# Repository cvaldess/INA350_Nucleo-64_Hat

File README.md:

# INA350 Nucleo-64 Hat

Test board that plugs onto an STM32 **NUCLEO-64** through the morpho connectors. It compares three
instrumentation amplifiers measuring the **same current shunt**:

- **TI INA350CDS** (U8)
- **Analog Devices AD8220** (U6)
- **Microchip MCP6N11-010** (U7)

The board reproduces one range of a current-measurement front end (shunt, bypass MOSFET and
protection). The three amplifiers can then be compared on real hardware before choosing one for a
power-measurement module. No oscilloscope is needed: the Nucleo is meant to sample the three outputs
at the same time with its own ADCs, synchronised with a load-step timer, and send the results over USB.

*Concept image, not a photo of an assembled board.*

| PCB layout | 3D view |
|---|---|
|  |  |

## Status

**Rev 0.1**: design finished and fabrication files generated. Not yet assembled or tested.
The test firmware is not written yet.

## Features

- Three amplifier channels (rows A, B, C) on one 4.99 kΩ 0.1 % shunt (R11, between VM and VOUT),
  each with its own Kelvin connection to the shunt.
- Shunt bypass MOSFET (Q1, AO3400A) driven by a UCC27524 gate driver (U4), controlled by the Nucleo.
- Loads on VOUT selected with jumpers JP2–JP6, including a step load (Q2 + R16 33 Ω, about 100 mA at
  3.3 V) switched by a timer output.
- Programmable measured voltage VM: adjustable TLV76701 LDO with the Nucleo DAC injected into its
  feedback (about 0.8 V to 5.3 V). Open JP1 to feed an external VM on J2 instead.
- Local rails from 12 V: +10V_G and +5V5_A (TLV76701 LDOs). A TLV9002 buffers the 0.30 V amplifier
  reference and VOUT.
- 12 V input through a DC jack (J5) or a 2-pin header (J1), with an SS34 series diode and a 470 µF bulk
  capacitor.
- Test points on every relevant node and six jumpers to configure the channels.

## Board

- 70 × 53 mm, 4 layers (In1 power, In2 signal), green solder mask.
- 2×19 sockets (HC-PM254-8.5H) on the bottom side; the board sits about 11 mm above the Nucleo.
- Two 3 mm notches on the top edge leave room for the Nucleo user and reset buttons (B1/B2).
- Fine-pitch parts use `_PCBWay` footprint variants (solder-mask web ≥ 0.19 mm between pads).

## Compatible Nucleo boards

| Board | Notes |
|---|---|
| NUCLEO-G474RE (MB1367) | Move **JP8 to [2-3]** so that VREF+ = VDD. With the factory VREF+ of 2.5 V the full output range does not fit. |
| NUCLEO-G564RE (MB2067) | Works as is. The DAC output is on PA5 instead of PA4. |

No solder bridges need to be changed on either board.

## Nucleo pin mapping

| Signal | Morpho pin | MCU pin | Use |
|---|---|---|---|
| O_A, AD8220 output | CN7-30 | PA1 | ADC / COMP1 |
| O_B, MCP6N11-010 output | CN7-28 | PA0 | ADC / COMP3 |
| O_C, INA350 output | CN7-34 | PB0 | ADC / COMP4 |
| DAC_VM, VM setpoint | CN7-32 | PA4 (G474RE) / PA5 (G564RE) | DAC |
| VOUT_S, output voltage sense | CN7-36 | PC1 | ADC |
| VM_S, VM sense | CN7-38 | PC0 | ADC |
| LOAD, load step | CN10-31 | PB3 | TIM2_CH2 |
| BYP0, shunt bypass | CN10-5 | PB9 | GPIO |
| +3V3 | CN7-16 | | |
| GND | CN7-8/19/20/22, CN10-9/20 | | |

## Repository layout

```
kicad/                          KiCad 10 project (schematic, PCB, design rules)
kicad/lib/                      project libraries: symbols, footprints and 3D models used by the board
fabrication/2026-11-17_rev0.1/  Gerbers + drill files (folder and zip), BOM, pick-and-place
images/                         README images
```

Open `kicad/PRUEBA_INA.kicad_pro` with **KiCad 10.0** or newer. The project keeps its original internal
name (`PRUEBA_INA`, Spanish for "INA test"). Part of the schematic text is in Spanish.

## Manufacturing notes

- `PRUEBA_INA_gerbers.zip` is ready to upload to a PCB fab (4 layers, 1.6 mm).
- The BOM lists LCSC part numbers where available. Generic 0603 passives have no part number.
- Test points are pads only and are not in the BOM.

## License

Copyright © 2026 CValdesS.com

This hardware design is licensed under the **CERN Open Hardware Licence Version 2 – Strongly
Reciprocal** (CERN-OHL-S-2.0). See [LICENSE](LICENSE).

Footprints and 3D models in `kicad/lib/easyeda2kicad.*` were converted from the LCSC/EasyEDA library
with [easyeda2kicad](https://github.com/uPesy/easyeda2kicad.py) and are included for convenience.

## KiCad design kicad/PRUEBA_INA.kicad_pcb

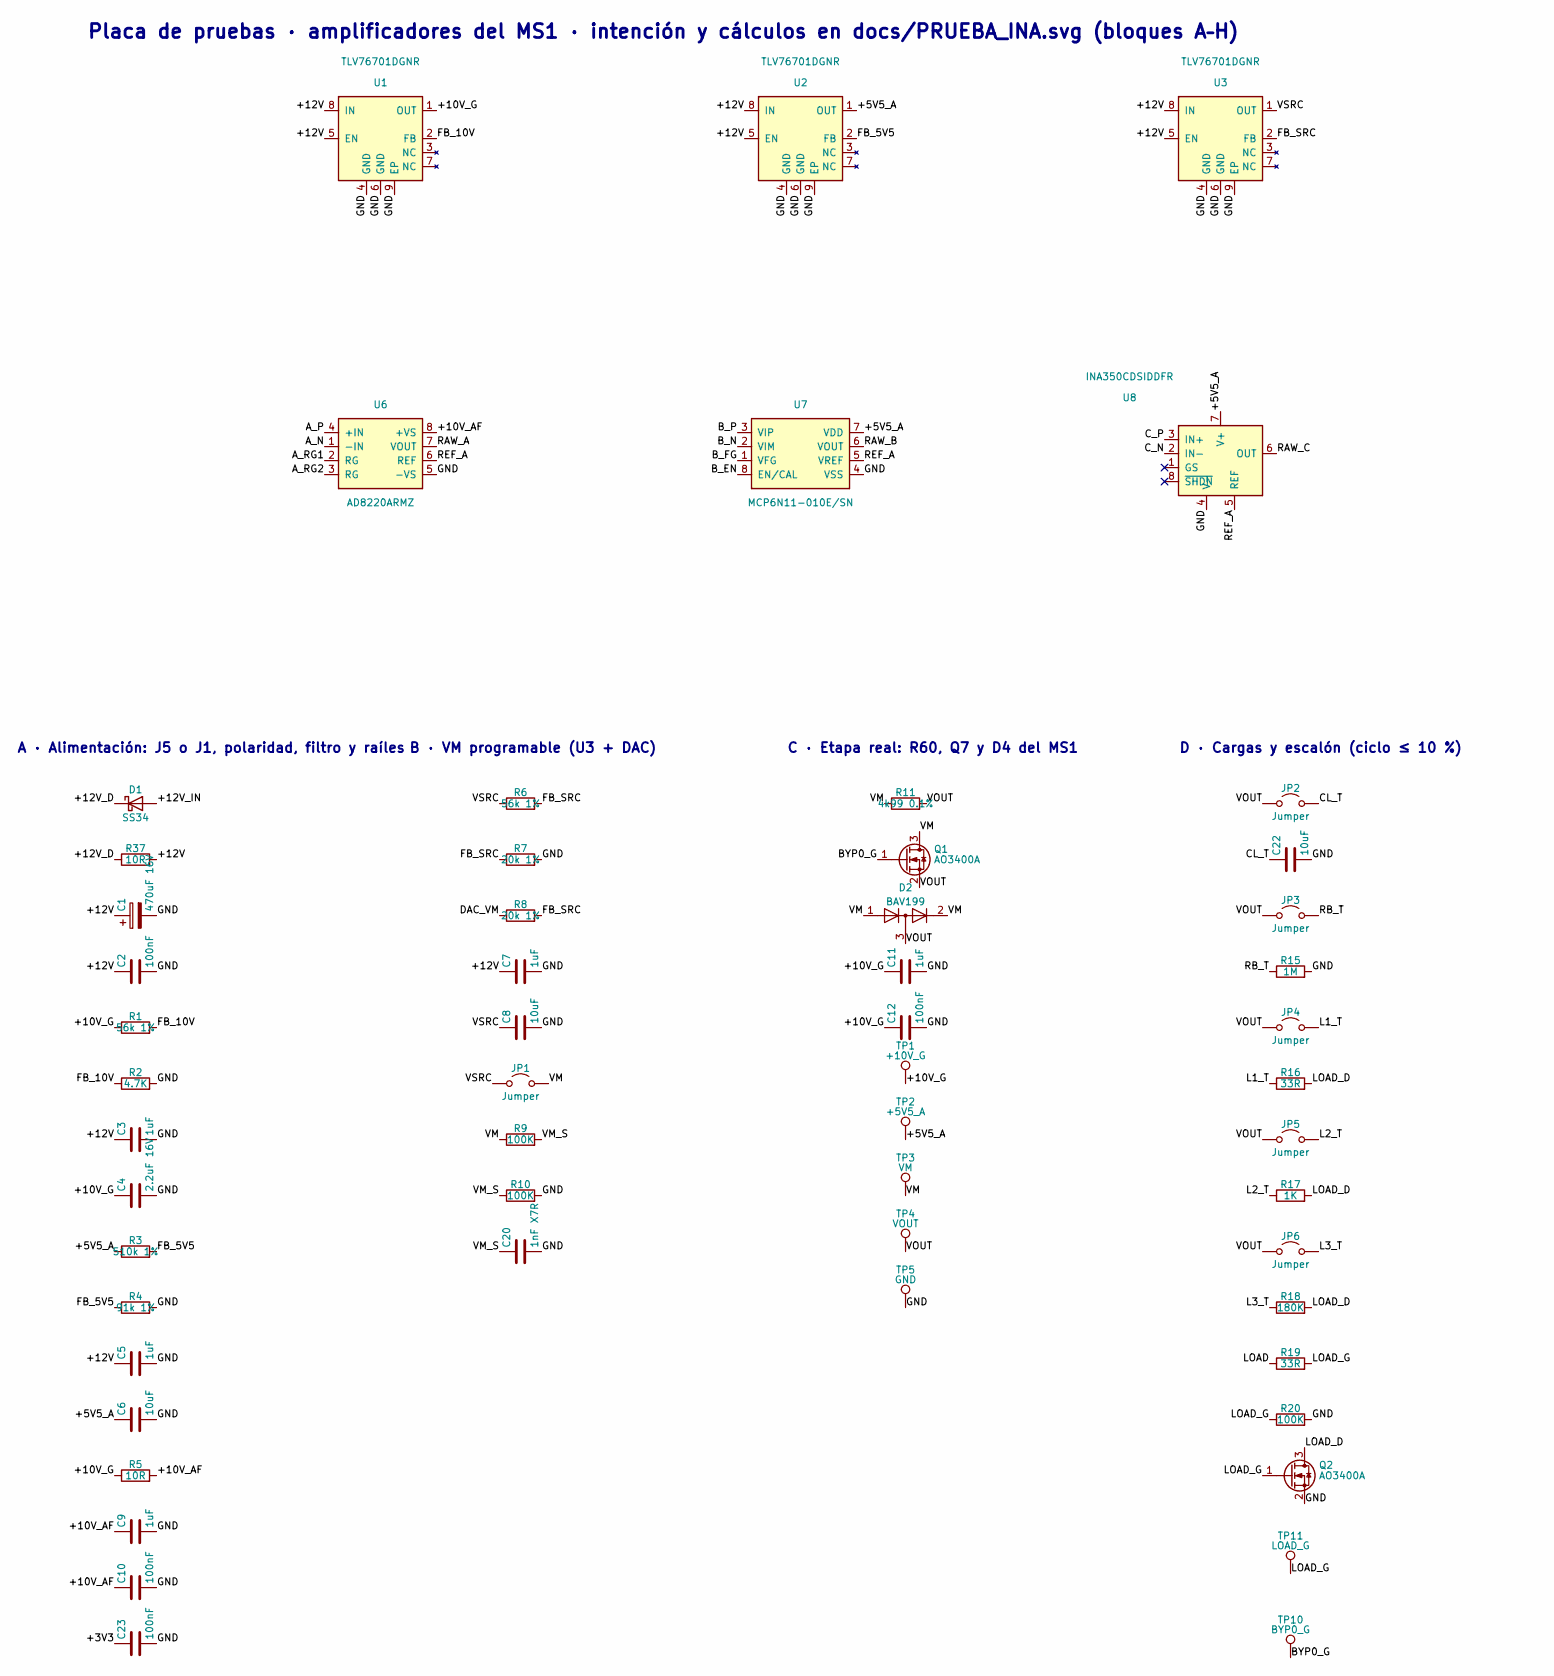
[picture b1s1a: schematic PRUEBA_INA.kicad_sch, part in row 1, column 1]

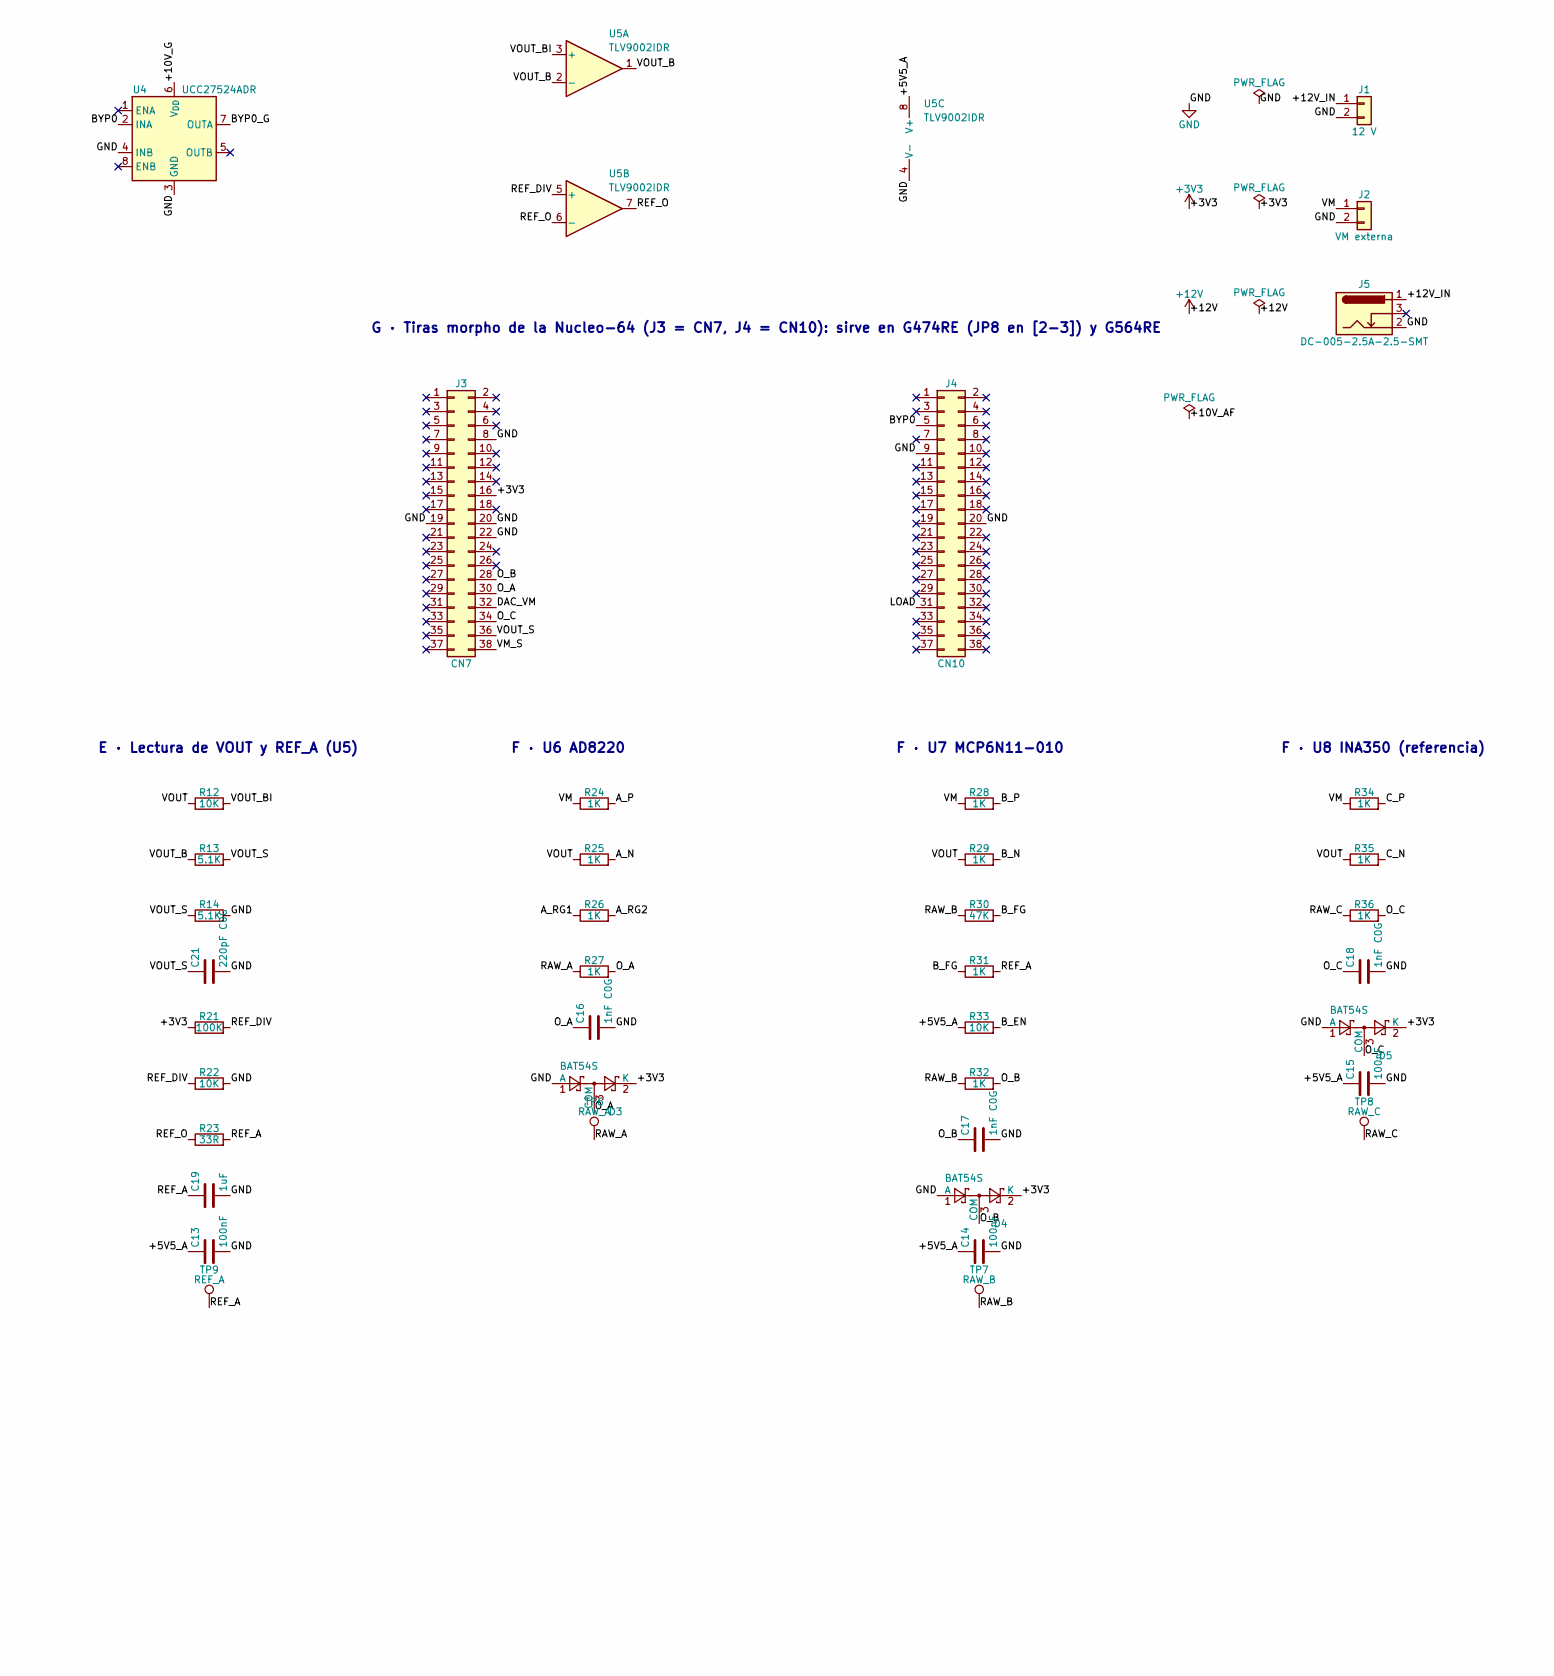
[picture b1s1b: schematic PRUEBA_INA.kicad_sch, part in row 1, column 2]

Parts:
C1: 470uF 16V; CP_Elec_6.3x7.7; MPN HV1C477M0607PZ; LCSC Part C42436549
C2, C10, C12, C13, C14, C15, C23: 100nF; C_0603_1608Metric
C3, C5, C7, C9, C11, C19: 1uF; C_0603_1608Metric
C4: 2.2uF 16V; C_0603_1608Metric; MPN CL10A225KO8NNNC; LCSC Part C23630
C6, C8: 10uF; C_0603_1608Metric
C16, C17, C18: 1nF C0G; C_0805_2012Metric; MPN 0805CG102J500NT; LCSC Part C29925
C20: 1nF X7R; C_0603_1608Metric; MPN CC0603KRX7R9BB102; LCSC Part C100040
C21: 220pF C0G; C_0402_1005Metric; MPN TCC0402COG221J500AT; LCSC Part C2994655
C22: 10uF; C_0805_2012Metric
D1: SS34; D_SMA; MPN SS34; LCSC Part C2837271
D2: BAV199; SOT-23; MPN BAV199,215; LCSC Part C40919
D3, D4, D5: BAT54S; SOT-23; MPN BAT54S,215; LCSC Part C47546
J1: 12 V; PinHeader_1x02_P2.54mm_Vertical
J2: VM externa; PinHeader_1x02_P2.54mm_Vertical
J3: CN7; PinSocket_2x19_P2.54mm_Vertical; MPN HC-PM254-8.5H-2x19PZ; LCSC Part C22373924
J4: CN10; PinSocket_2x19_P2.54mm_Vertical; MPN HC-PM254-8.5H-2x19PZ; LCSC Part C22373924
J5: DC-005-2.5A-2.5-SMT; DC-IN-TH_XKB_DC-005-2.5A-2.5-SMT; MPN DC-005-2.5A-2.5-SMT; LCSC Part C2880544
JP1, JP2, JP3, JP4, JP5, JP6: Jumper; PinHeader_1x02_P2.54mm_Vertical
Q1, Q2: AO3400A; SOT-23; MPN AO3400A; LCSC Part C20917
R1, R6: 56k 1%; R_0603_1608Metric; MPN FRC0603F5602TS; LCSC Part C2907053
R2: 4.7K; R_0603_1608Metric
R3: 510k 1%; R_0603_1608Metric; MPN FRC0603F5103TS; LCSC Part C2907047
R4: 91k 1%; R_0603_1608Metric; MPN FRC0603F9102TS; LCSC Part C2907077
R5, R37: 10R; R_0603_1608Metric
R7, R8: 20k 1%; R_0603_1608Metric; MPN FRC0603F2002TS; LCSC Part C2907011
R9, R10, R20, R21: 100K; R_0603_1608Metric
R11: 4k99 0.1%; R_0805_2012Metric; MPN RT0805BRD074K99L; LCSC Part C706246
R12, R22, R33: 10K; R_0603_1608Metric
R13, R14: 5.1K; R_0603_1608Metric
R15: 1M; R_0603_1608Metric
R16, R19, R23: 33R; R_0603_1608Metric
R17, R24, R25, R26, R27, R28, R29, R31, R32, R34, R35, R36: 1K; R_0603_1608Metric
R18: 180K; R_0603_1608Metric
R30: 47K; R_0603_1608Metric
TP1: +10V_G; TestPoint_Pad_D1.5mm
TP2: +5V5_A; TestPoint_Pad_D1.5mm
TP3: VM; TestPoint_Pad_D1.5mm
TP4: VOUT; TestPoint_Pad_D1.5mm
TP5: GND; TestPoint_Pad_D1.5mm
TP6: RAW_A; TestPoint_Pad_D1.5mm
TP7: RAW_B; TestPoint_Pad_D1.5mm
TP8: RAW_C; TestPoint_Pad_D1.5mm
TP9: REF_A; TestPoint_Pad_D1.5mm
TP10: BYP0_G; TestPoint_Pad_D1.5mm
TP11: LOAD_G; TestPoint_Pad_D1.5mm
U1, U2, U3: TLV76701DGNR; HVSSOP-8-1EP_3x3mm_P0.65mm_EP1.57x1.89mm_ThermalVias_PCBWay; MPN TLV76701DGNR; LCSC Part C3752401
U4: UCC27524ADR; SOIC-8_3.9x4.9mm_P1.27mm; MPN UCC27524ADR; LCSC Part C185857
U5: TLV9002IDR; SOIC-8_3.9x4.9mm_P1.27mm; MPN TLV9002IDR; LCSC Part C398360
U6: AD8220ARMZ; MSOP-8_3x3mm_P0.65mm; MPN AD8220ARMZ
U7: MCP6N11-010E/SN; SOIC-8_3.9x4.9mm_P1.27mm; MPN MCP6N11-010E/SN; LCSC Part C636377
U8: INA350CDSIDDFR; SOT-23-8_PCBWay; MPN INA350CDSIDDFR; LCSC Part C5213940

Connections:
+3V3: C23.1, D3.2 (K), D4.2 (K), D5.2 (K), J3.16, R21.1
+12V: C1.1, C2.1, C3.1, C5.1, C7.1, R37.2, U1.5 (EN), U1.8 (IN), U2.5 (EN), U2.8 (IN), U3.5 (EN), U3.8 (IN)
/+5V5_A: C6.1, C13.1, C14.1, C15.1, R3.1, R33.1, TP2.1 (1_1), U2.1 (OUT), U5.8 (V+), U7.7 (VDD), U8.7 (V+)
/+10V_AF: C9.1, C10.1, R5.2, U6.8 (+VS)
/+10V_G: C4.1, C11.1, C12.1, R1.1, R5.1, TP1.1 (1_1), U1.1 (OUT), U4.6 (V_{DD})
/+12V_D: D1.1 (K), R37.1
/+12V_IN: D1.2 (A), J1.1, J5.1
/A_N: R25.2, U6.1 (-IN)
/A_P: R24.2, U6.4 (+IN)
/A_RG1: R26.1, U6.2 (RG)
/A_RG2: R26.2, U6.3 (RG)
/BYP0: J4.5, U4.2 (INA)
/BYP0_G: Q1.1 (G), TP10.1 (1_1), U4.7 (OUTA)
/B_EN: R33.2, U7.8 (EN/CAL)
/B_FG: R30.2, R31.1, U7.1 (VFG)
/B_N: R29.2, U7.2 (VIM)
/B_P: R28.2, U7.3 (VIP)
/CL_T: C22.1, JP2.2 (B)
/C_N: R35.2, U8.2 (IN-)
/C_P: R34.2, U8.3 (IN+)
/DAC_VM: J3.32, R8.1
/FB_5V5: R3.2, R4.1, U2.2 (FB)
/FB_10V: R1.2, R2.1, U1.2 (FB)
/FB_SRC: R6.2, R7.1, R8.2, U3.2 (FB)
/L1_T: JP4.2 (B), R16.1
/L2_T: JP5.2 (B), R17.1
/L3_T: JP6.2 (B), R18.1
/LOAD: J4.31, R19.1
/LOAD_D: Q2.3 (D), R16.2, R17.2, R18.2
/LOAD_G: Q2.1 (G), R19.2, R20.1, TP11.1 (1_1)
/O_A: C16.1, D3.3 (COM), J3.30, R27.2
/O_B: C17.1, D4.3 (COM), J3.28, R32.2
/O_C: C18.1, D5.3 (COM), J3.34, R36.2
/RAW_A: R27.1, TP6.1 (1_1), U6.7 (VOUT)
/RAW_B: R30.1, R32.1, TP7.1 (1_1), U7.6 (VOUT)
/RAW_C: R36.1, TP8.1 (1_1), U8.6 (OUT)
/RB_T: JP3.2 (B), R15.1
/REF_A: C19.1, R23.2, R31.2, TP9.1 (1_1), U6.6 (REF), U7.5 (VREF), U8.5 (REF)
/REF_DIV: R21.2, R22.1, U5.5 (+)
/REF_O: R23.1, U5.6 (-), U5.7
/VM: D2.1 (K), D2.2 (A), J2.1, JP1.2 (B), Q1.3 (D), R9.1, R11.1, R24.1, R28.1, R34.1, TP3.1 (1_1)
/VM_S: C20.1, J3.38, R9.2, R10.1
/VOUT: D2.3 (K), JP2.1 (A), JP3.1 (A), JP4.1 (A), JP5.1 (A), JP6.1 (A), Q1.2 (S), R11.2, R12.1, R25.1, R29.1, R35.1, TP4.1 (1_1)
/VOUT_B: R13.1, U5.1, U5.2 (-)
/VOUT_BI: R12.2, U5.3 (+)
/VOUT_S: C21.1, J3.36, R13.2, R14.1
/VSRC: C8.1, JP1.1 (A), R6.1, U3.1 (OUT)
GND: C1.2, C2.2, C3.2, C4.2, C5.2, C6.2, C7.2, C8.2, C9.2, C10.2, C11.2, C12.2, C13.2, C14.2, C15.2, C16.2, C17.2, C18.2, C19.2, C20.2, C21.2, C22.2, C23.2, D3.1 (A), D4.1 (A), D5.1 (A), J1.2, J2.2, J3.8, J3.19, J3.20, J3.22, J4.9, J4.20, J5.2, Q2.2 (S), R2.2, R4.2, R7.2, R10.2, R14.2, R15.2, R20.2, R22.2, TP5.1 (1_1), U1.4 (GND), U1.6 (GND), U1.9 (EP), U2.4 (GND), U2.6 (GND), U2.9 (EP), U3.4 (GND), U3.6 (GND), U3.9 (EP), U4.3 (GND), U4.4 (INB), U5.4 (V-), U6.5 (-VS), U7.4 (VSS), U8.4 (V-)

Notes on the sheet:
C · Etapa real: R60, Q7 y D4 del MS1
F · U7 MCP6N11-010
G · Tiras morpho de la Nucleo-64 (J3 = CN7, J4 = CN10): sirve en G474RE (JP8 en [2-3]) y G564RE
F · U8 INA350 (referencia)
D · Cargas y escalón (ciclo ≤ 10 %)
F · U6 AD8220
Placa de pruebas · amplificadores del MS1 · intención y cálculos en docs/PRUEBA_INA.svg (bloques A–H)
A · Alimentación: J5 o J1, polaridad, filtro y raíles
E · Lectura de VOUT y REF_A (U5)
B · VM programable (U3 + DAC)

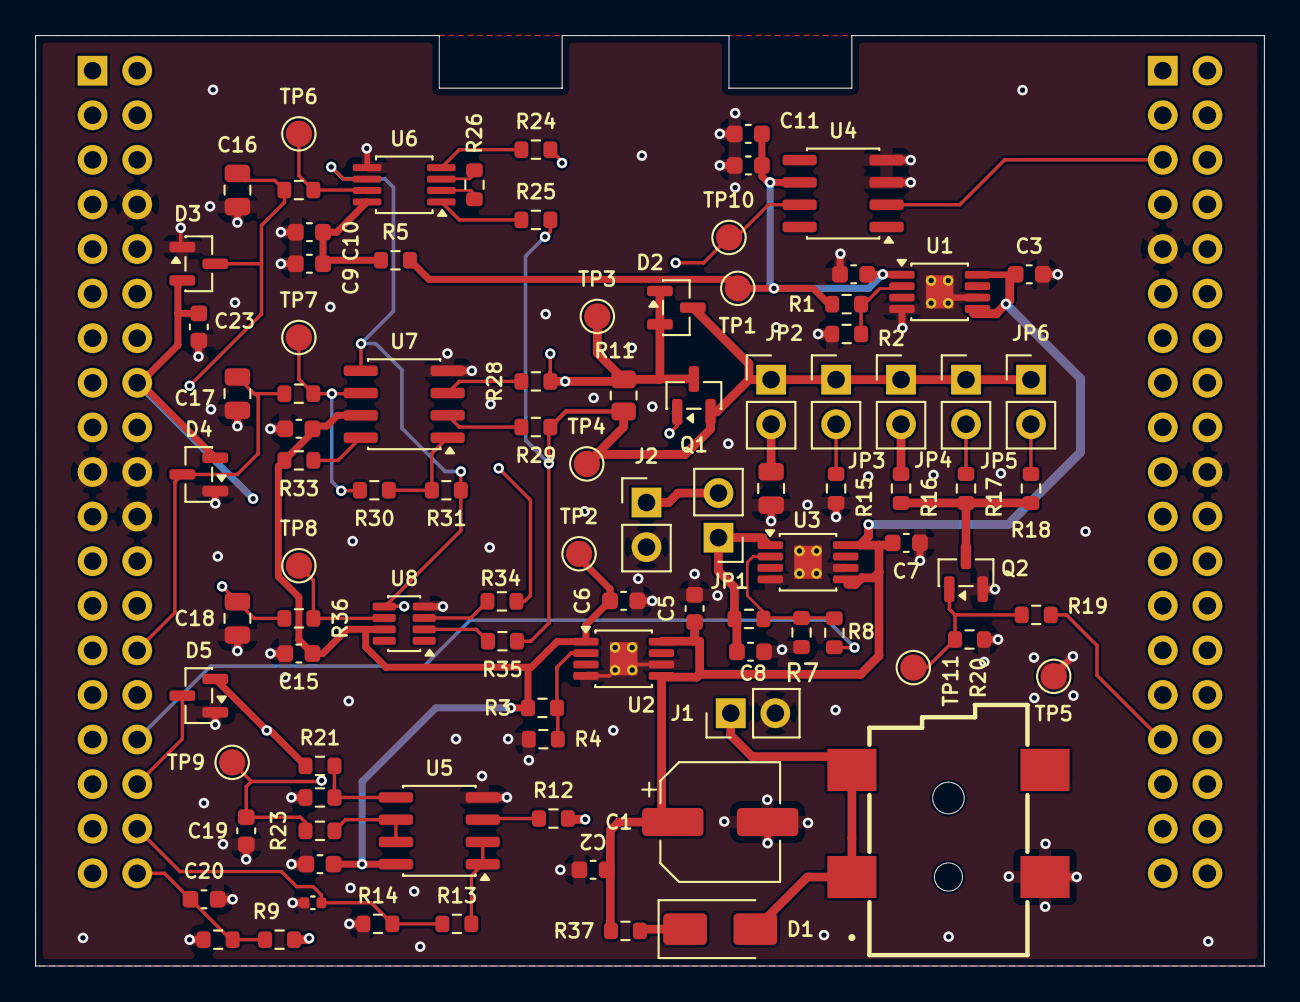
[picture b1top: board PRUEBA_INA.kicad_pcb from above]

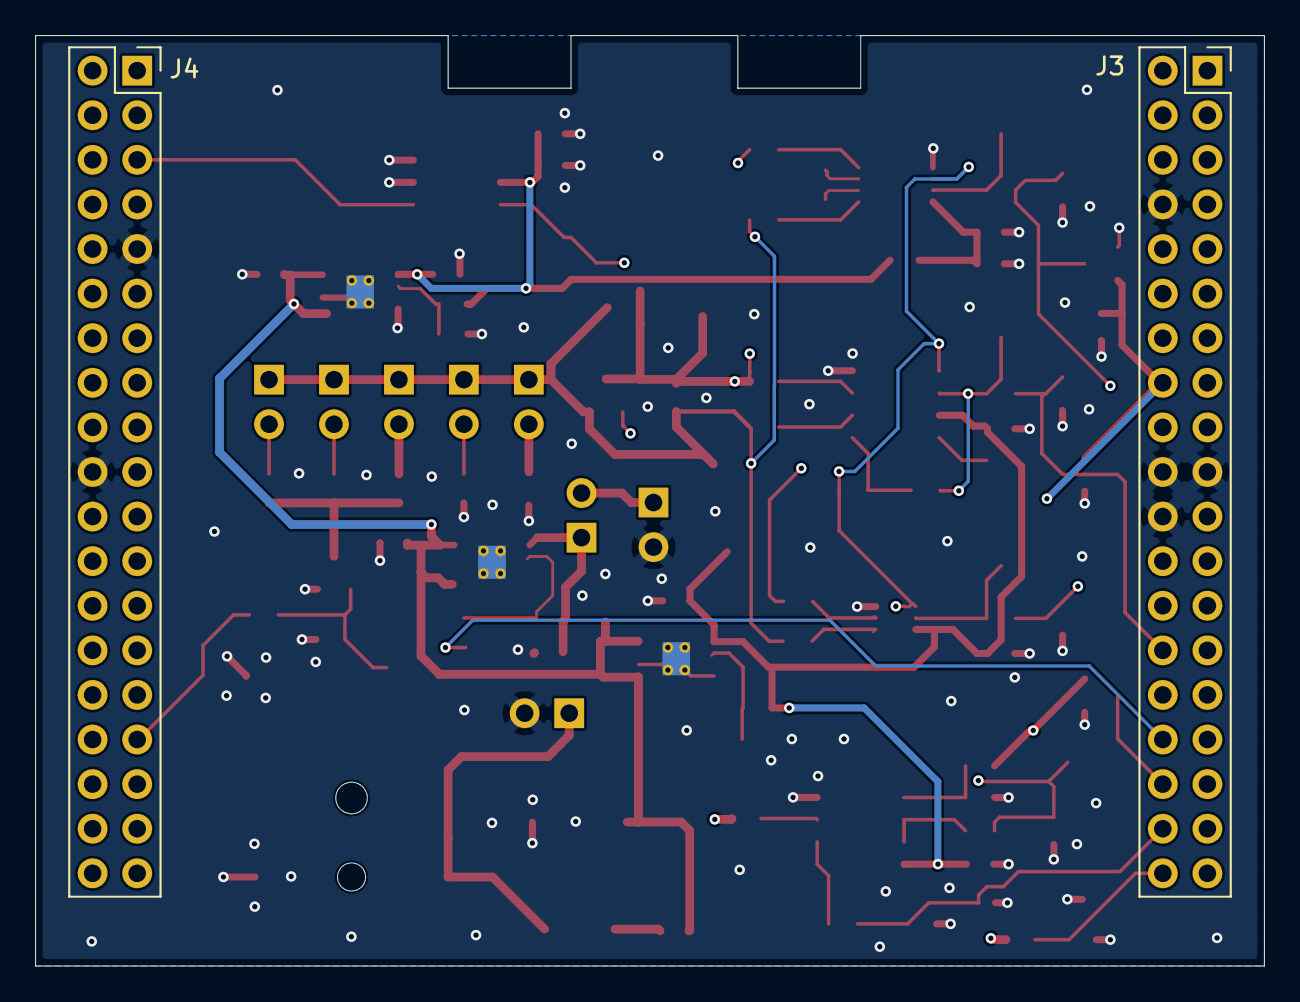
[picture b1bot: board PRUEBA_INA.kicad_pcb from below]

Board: 4 copper layers, 70.0 x 53.0 mm, 97 parts (2 on the bottom side), 48 nets.

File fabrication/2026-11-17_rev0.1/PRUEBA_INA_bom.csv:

"Reference","Value","Footprint","Qty","DNP","LCSC Part","MPN","Manufacturer"
"U1,U2,U3","TLV76701DGNR","HVSSOP-8","3","","C3752401","TLV76701DGNR","TI"
"U4","UCC27524ADR","SOIC-8","1","","C185857","UCC27524ADR","TI"
"U5","TLV9002IDR","SOIC-8","1","","C398360","TLV9002IDR","TI"
"U6","AD8220ARMZ","MSOP-8","1","","","AD8220ARMZ","Analog Devices"
"U7","MCP6N11-010E/SN","SOIC-8","1","","C636377","MCP6N11-010E/SN","Microchip"
"U8","INA350CDSIDDFR","SOT-23-8","1","","C5213940","INA350CDSIDDFR","TI"
"Q1,Q2","AO3400A","SOT-23","2","","C20917","AO3400A","AOS"
"D1","SS34","SMA","1","","C2837271","SS34","JSMSEMI"
"D2","BAV199","SOT-23","1","","C40919","BAV199,215","Nexperia"
"D3,D4,D5","BAT54S","SOT-23","3","","C47546","BAT54S,215","Nexperia"
"J3,J4","Zocalo 2x19 2.54","THT","2","","C22373924","HC-PM254-8.5H-2x19PZ","Hong Cheng"
"J5","DC-005-2.5A-2.5-SMT","SMD","1","","C2880544","DC-005-2.5A-2.5-SMT","XKB Connection"
"R11","4k99 0.1%","0805","1","","C706246","RT0805BRD074K99L","YAGEO"
"R1,R6","56k 1%","0603","2","","C2907053","FRC0603F5602TS","FOJAN"
"R2","4.7K","0603","1","","","",""
"R3","510k 1%","0603","1","","C2907047","FRC0603F5103TS","FOJAN"
"R4","91k 1%","0603","1","","C2907077","FRC0603F9102TS","FOJAN"
"R7,R8","20k 1%","0603","2","","C2907011","FRC0603F2002TS","FOJAN"
"R9,R10,R20,R21","100K","0603","4","","","",""
"R12,R22,R33","10K","0603","3","","","",""
"R13,R14","5.1K","0603","2","","","",""
"R17,R24,R25,R26,R27,R28,R29,R31,R32,R34,R35,R36","1K","0603","12","","","",""
"R30","47K","0603","1","","","",""
"R15","1M","0603","1","","","",""
"R18","180K","0603","1","","","",""
"R16,R19,R23","33R","0603","3","","","",""
"R5,R37","10R","0603","2","","","",""
"C1","470uF 16V","SMD D6.3x7.7","1","","C42436549","HV1C477M0607PZ","Honor Elec"
"C2,C10,C12,C13,C14,C15,C23","100nF","0603","7","","","",""
"C3,C5,C7,C9,C11,C19","1uF","0603","6","","","",""
"C4","2.2uF 16V","0603","1","","C23630","CL10A225KO8NNNC","Samsung"
"C6,C8","10uF","0603","2","","","",""
"C22","10uF","0805","1","","","",""
"C16,C17,C18","1nF C0G","0805","3","","C29925","0805CG102J500NT","FH"
"C20","1nF X7R","0603","1","","C100040","CC0603KRX7R9BB102","YAGEO"
"C21","220pF C0G","0402","1","","C2994655","TCC0402COG221J500AT","CCTC"
"JMP1,JMP2,JMP3,JMP4,JMP5,JMP6","Jumper 2.54","THT","6","","C2689176","F254D-02-065-PT-B","XFCN"
